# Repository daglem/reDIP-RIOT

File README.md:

# reDIP RIOT

## MOS 6530 RRIOT / MOS 6532 RIOT FPGA replacement

## Overview
The reDIP RIOT is an open source FPGA board which combines the following in a DIP-40 size package:

* Lattice iCE40UP5K FPGA
* 1Mbit FLASH
* 5V tolerant I/O

The reDIP RIOT provides an open source hardware platform for 6530 RRIOT / MOS 6532 RIOT replacements.

Designs for the iCE40UP5K FPGA can be processed by [yosys](https://github.com/YosysHQ/yosys/) and [nextpnr](https://github.com/YosysHQ/nextpnr/).

## I/O interfaces

### DIP-40 header pins:

* 5V input
* 35 FPGA GPIO
* 3 FPGA open-drain I/O
* GND

All FPGA header I/O is 5V tolerant, and can drive 5V TTL.

### SPI / programming header:

A separate header footprint is provided for (Q)SPI flash programming, with pinout borrowed from the [iCEBreaker Bitsy](https://github.com/icebreaker-fpga/icebreaker).

## Board Front

## Board Back

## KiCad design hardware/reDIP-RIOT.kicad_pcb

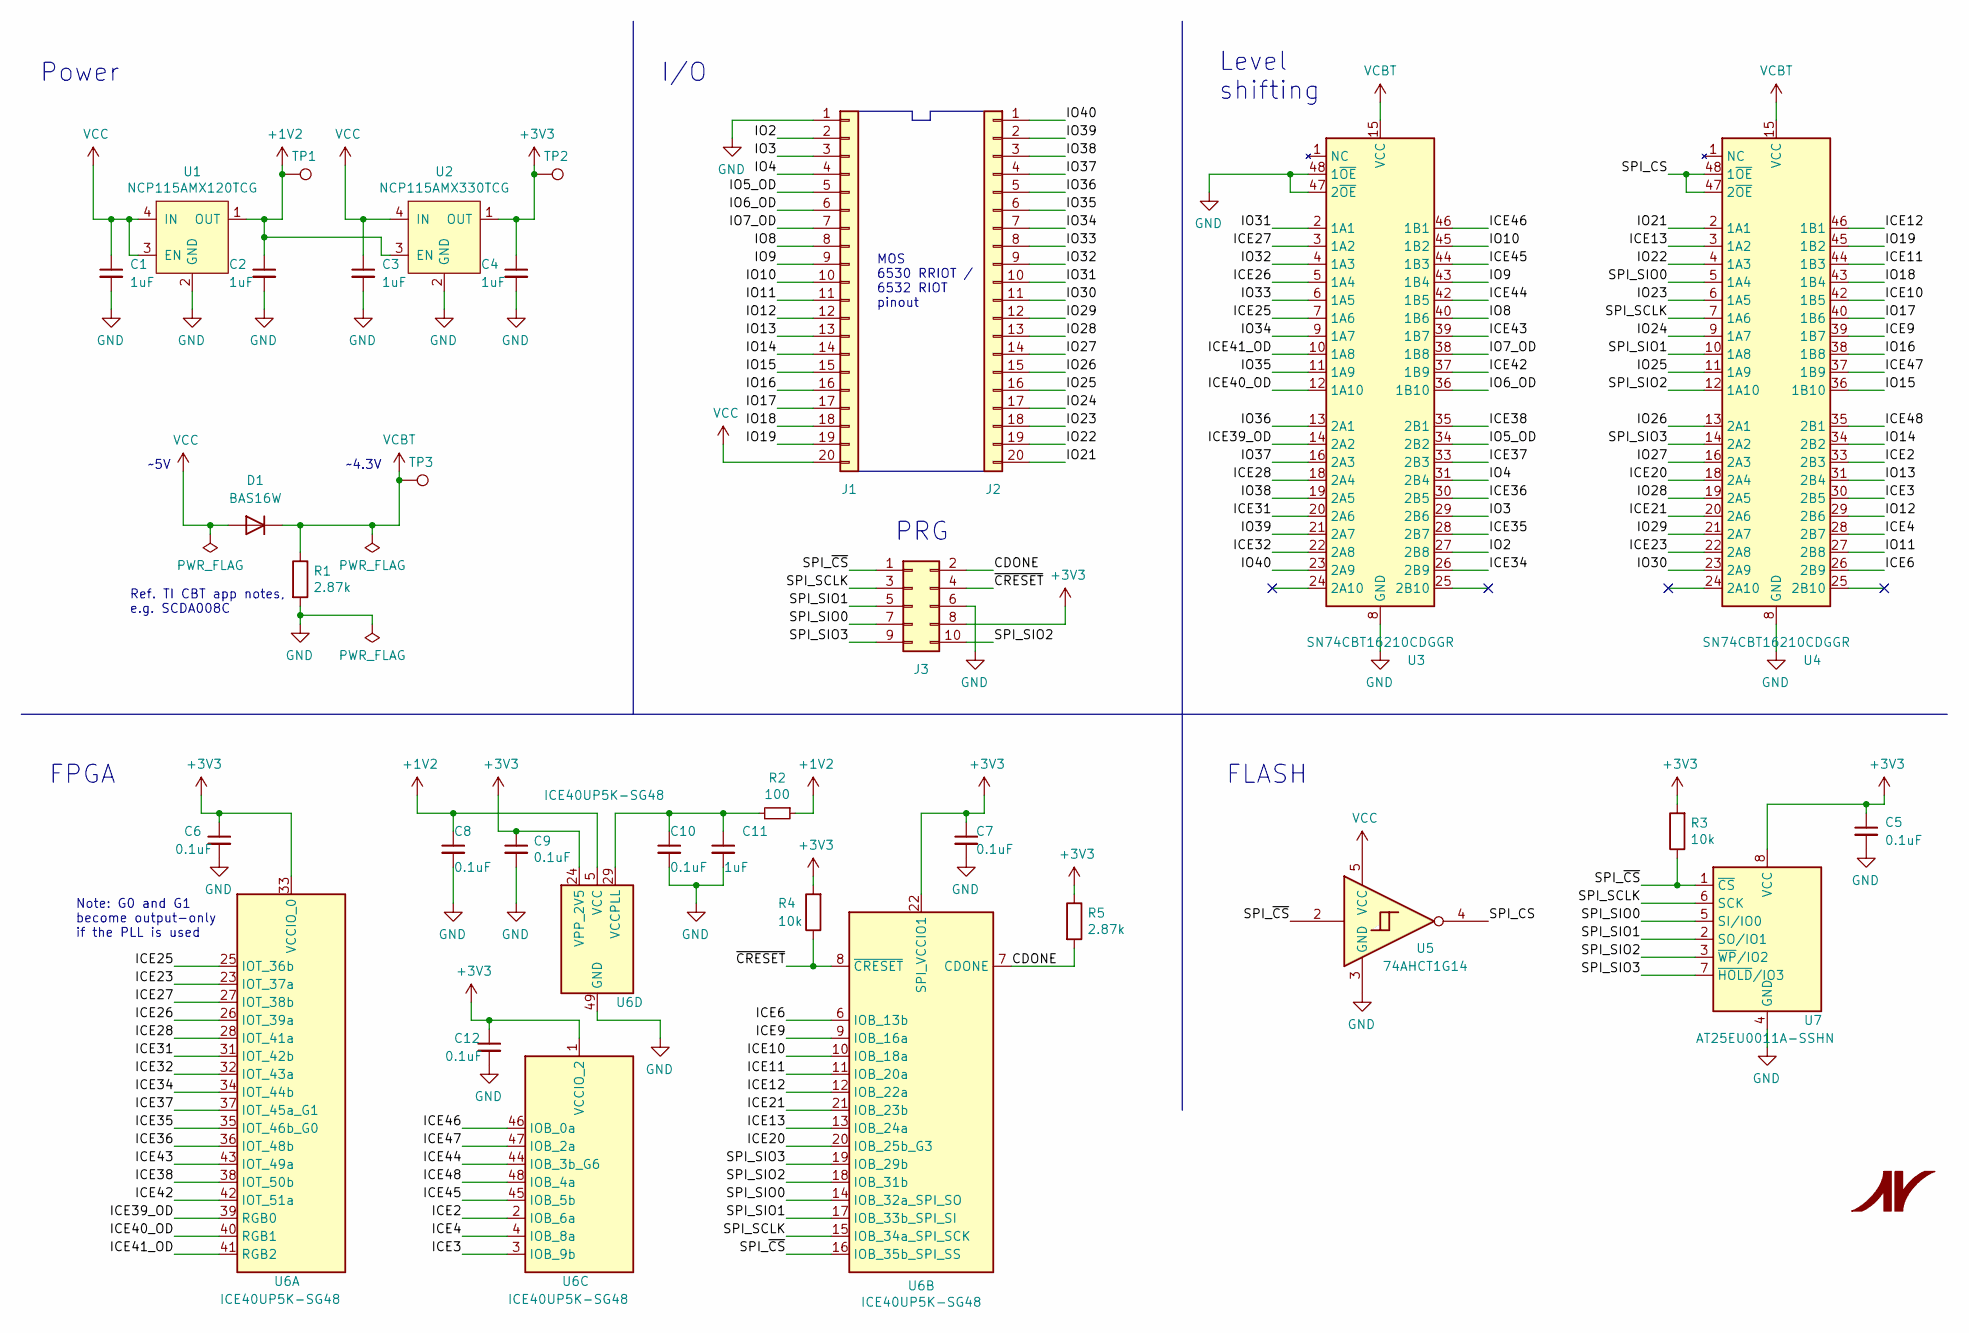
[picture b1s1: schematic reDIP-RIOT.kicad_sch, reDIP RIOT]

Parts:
C1, C3: 1uF; C_0402_1005Metric
C2, C4, C11: 1uF; C_0201_0603Metric
C5, C6, C7, C8, C9, C10, C12: 0.1uF; C_0201_0603Metric
D1: BAS16W; SOT-323_SC-70
J1, J2: Conn_01x20; PinHeader_1x20_P2.54mm_Vertical_Machined
J3: Conn_02x05_Odd_Even; PinHeader_2x05_P2.54mm_Vertical
R1, R5: 2.87k; R_0201_0603Metric
R2: 100; R_0201_0603Metric
R3, R4: 10k; R_0201_0603Metric
TP1, TP2, TP3: TestPoint; TestPoint_Pad_D1.00mm
U1: NCP115AMX120TCG; CASE_711AJ_1.0x1.0mm_P0.65mm
U2: NCP115AMX330TCG; CASE_711AJ_1.0x1.0mm_P0.65mm
U3, U4: SN74CBT16210CDGGR; TSSOP-48_6.1x12.5mm_P0.5mm
U5: 74AHCT1G14; SOT-353_SC-70-5
U6: ICE40UP5K-SG48; QFN-48-1EP_7x7mm_P0.5mm_EP5.6x5.6mm
U7: AT25EU0011A-SSHN; SOIC-8_3.9x4.9mm_P1.27mm

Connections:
+1V2: C2.1, C8.1, R2.1, TP1.1, U1.1 (OUT), U2.3 (EN), U6.5 (VCC), U6.30 (VCC)
+3V3: C4.1, C5.1, C6.1, C7.1, C9.1, C12.1, J3.8, R3.2, R4.2, R5.1, TP2.1, U2.1 (OUT), U6.1 (VCCIO_2), U6.22 (SPI_VCCIO1), U6.24 (VPP_2V5), U6.33 (VCCIO_0), U7.8 (VCC)
/CDONE: J3.2, R5.2, U6.7 (CDONE)
/ICE2: U4.33 (2B3), U6.2 (IOB_6a)
/ICE3: U4.30 (2B5), U6.3 (IOB_9b)
/ICE4: U4.28 (2B7), U6.4 (IOB_8a)
/ICE6: U4.26 (2B9), U6.6 (IOB_13b)
/ICE9: U4.39 (1B7), U6.9 (IOB_16a)
/ICE10: U4.42 (1B5), U6.10 (IOB_18a)
/ICE11: U4.44 (1B3), U6.11 (IOB_20a)
/ICE12: U4.46 (1B1), U6.12 (IOB_22a)
/ICE13: U4.3 (1A2), U6.13 (IOB_24a)
/ICE20: U4.18 (2A4), U6.20 (IOB_25b_G3)
/ICE21: U4.20 (2A6), U6.21 (IOB_23b)
/ICE23: U4.22 (2A8), U6.23 (IOT_37a)
/ICE25: U3.7 (1A6), U6.25 (IOT_36b)
/ICE26: U3.5 (1A4), U6.26 (IOT_39a)
/ICE27: U3.3 (1A2), U6.27 (IOT_38b)
/ICE28: U3.18 (2A4), U6.28 (IOT_41a)
/ICE31: U3.20 (2A6), U6.31 (IOT_42b)
/ICE32: U3.22 (2A8), U6.32 (IOT_43a)
/ICE34: U3.26 (2B9), U6.34 (IOT_44b)
/ICE35: U3.28 (2B7), U6.35 (IOT_46b_G0)
/ICE36: U3.30 (2B5), U6.36 (IOT_48b)
/ICE37: U3.33 (2B3), U6.37 (IOT_45a_G1)
/ICE38: U3.35 (2B1), U6.38 (IOT_50b)
/ICE39_OD: U3.14 (2A2), U6.39 (RGB0)
/ICE40_OD: U3.12 (1A10), U6.40 (RGB1)
/ICE41_OD: U3.10 (1A8), U6.41 (RGB2)
/ICE42: U3.37 (1B9), U6.42 (IOT_51a)
/ICE43: U3.39 (1B7), U6.43 (IOT_49a)
/ICE44: U3.42 (1B5), U6.44 (IOB_3b_G6)
/ICE45: U3.44 (1B3), U6.45 (IOB_5b)
/ICE46: U3.46 (1B1), U6.46 (IOB_0a)
/ICE47: U4.37 (1B9), U6.47 (IOB_2a)
/ICE48: U4.35 (2B1), U6.48 (IOB_4a)
/IO2: J1.2, U3.27 (2B8)
/IO3: J1.3, U3.29 (2B6)
/IO4: J1.4, U3.31 (2B4)
/IO5_OD: J1.5, U3.34 (2B2)
/IO6_OD: J1.6, U3.36 (1B10)
/IO7_OD: J1.7, U3.38 (1B8)
/IO8: J1.8, U3.40 (1B6)
/IO9: J1.9, U3.43 (1B4)
/IO10: J1.10, U3.45 (1B2)
/IO11: J1.11, U4.27 (2B8)
/IO12: J1.12, U4.29 (2B6)
/IO13: J1.13, U4.31 (2B4)
/IO14: J1.14, U4.34 (2B2)
/IO15: J1.15, U4.36 (1B10)
/IO16: J1.16, U4.38 (1B8)
/IO17: J1.17, U4.40 (1B6)
/IO18: J1.18, U4.43 (1B4)
/IO19: J1.19, U4.45 (1B2)
/IO21: J2.20, U4.2 (1A1)
/IO22: J2.19, U4.4 (1A3)
/IO23: J2.18, U4.6 (1A5)
/IO24: J2.17, U4.9 (1A7)
/IO25: J2.16, U4.11 (1A9)
/IO26: J2.15, U4.13 (2A1)
/IO27: J2.14, U4.16 (2A3)
/IO28: J2.13, U4.19 (2A5)
/IO29: J2.12, U4.21 (2A7)
/IO30: J2.11, U4.23 (2A9)
/IO31: J2.10, U3.2 (1A1)
/IO32: J2.9, U3.4 (1A3)
/IO33: J2.8, U3.6 (1A5)
/IO34: J2.7, U3.9 (1A7)
/IO35: J2.6, U3.11 (1A9)
/IO36: J2.5, U3.13 (2A1)
/IO37: J2.4, U3.16 (2A3)
/IO38: J2.3, U3.19 (2A5)
/IO39: J2.2, U3.21 (2A7)
/IO40: J2.1, U3.23 (2A9)
/SPI_CS: U4.47 (2~OE), U4.48 (1~OE), U5.4
/SPI_SCLK: J3.3, U4.7 (1A6), U6.15 (IOB_34a_SPI_SCK), U7.6 (SCK)
/SPI_SIO0: J3.7, U4.5 (1A4), U6.14 (IOB_32a_SPI_SO), U7.5 (SI/IO0)
/SPI_SIO1: J3.5, U4.10 (1A8), U6.17 (IOB_33b_SPI_SI), U7.2 (SO/IO1)
/SPI_SIO2: J3.10, U4.12 (1A10), U6.18 (IOB_31b), U7.3 (~WP/IO2)
/SPI_SIO3: J3.9, U4.14 (2A2), U6.19 (IOB_29b), U7.7 (~HOLD/IO3)
/SPI_~CS: J3.1, R3.1, U5.2, U6.16 (IOB_35b_SPI_SS), U7.1 (~CS)
/~CRESET: J3.4, R4.1, U6.8 (~CRESET)
GND: C1.2, C2.2, C3.2, C4.2, C5.2, C6.2, C7.2, C8.2, C9.2, C10.2, C11.2, C12.2, J1.1, J3.6, R1.2, U1.2 (GND), U2.2 (GND), U3.8 (GND), U3.17 (GND), U3.32 (GND), U3.41 (GND), U3.47 (2~OE), U3.48 (1~OE), U4.8 (GND), U4.17 (GND), U4.32 (GND), U4.41 (GND), U5.3 (GND), U6.49 (GND), U7.4 (GND)
unnamed: C10.1, C11.1, R2.2, U6.29 (VCCPLL)
VCBT: D1.3 (K), R1.1, TP3.1, U3.15 (VCC), U4.15 (VCC)
VCC: C1.1, C3.1, D1.1 (A), J1.20, U1.3 (EN), U1.4 (IN), U2.4 (IN), U5.5 (VCC)

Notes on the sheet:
MOS 6530 RRIOT / 6532 RIOT pinout
PRG
Ref. TI CBT app notes, e.g. SCDA008C
~4.3V
FLASH
FPGA
Power
I/O
Level shifting
~5V
Note: G0 and G1 become output-only if the PLL is used

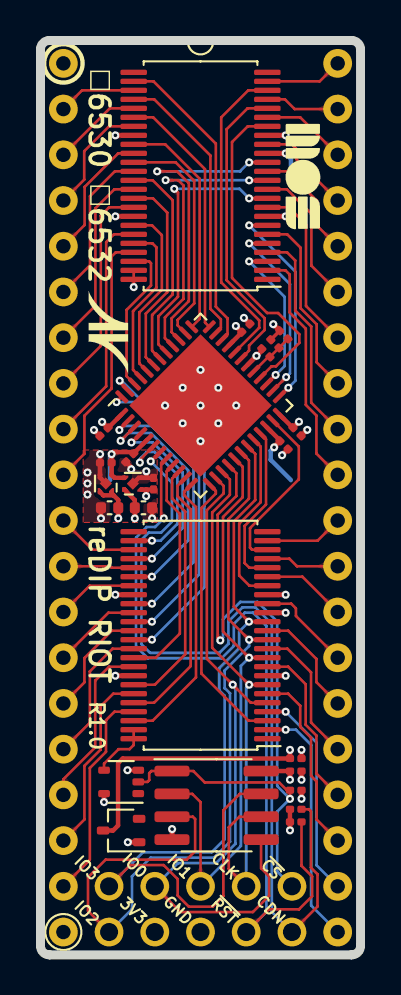
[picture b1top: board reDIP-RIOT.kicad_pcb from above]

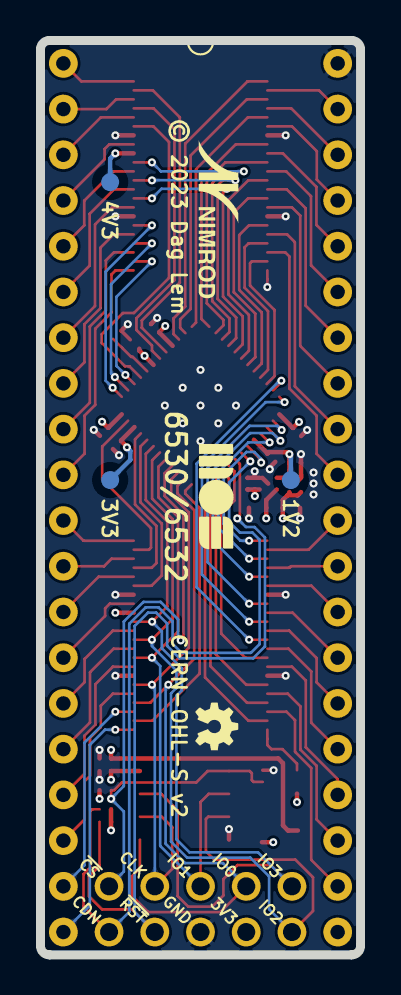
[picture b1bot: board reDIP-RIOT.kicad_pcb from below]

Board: 4 copper layers, 17.8 x 50.8 mm, 40 parts (14 on the bottom side), 86 nets.

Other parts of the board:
SolderMask_D0.25mm, SolderMask_D0.25mm#2, SolderMask_D0.25mm#3, SolderMask_D0.25mm#4, SolderMask_D0.25mm#5, SolderMask_D0.25mm#6, SolderMask_D0.25mm#7, SolderMask_D0.25mm#8, SolderMask_D0.25mm#9: SolderMask_D0.25mm

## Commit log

2023-10-02 Added CRESET pull-up, removed CDONE LED
2023-10-03 Cleanup
    * Removed unused footprints
    * Rounded rectangle pads for SOT footprints
    * Increased drill to 0.8mm for header pins
    * Corrected BOM text
2023-10-04 Added example pin headers to BOM
2023-10-06 LDO ground planes, via teardrops
2023-10-06 Use 74AHCT1G14 for better signal level margins
2023-10-09 Power supply for 74AHCT1G14 within range
2023-11-04 Replaced iCE5LP1K with iCE40UP5K
    The MOS 6530 and MOS 6532 have on-chip data port pull-up resistors
    in the range of 5k.
    While the iCE40UP5K features configurable 3.3k/6.8k/10k/100k pull-up
    resistors, the iCE5LP1K only features 100k pull-up resistors.
    We make the simple fix of using the more capable (and somewhat more
    expensive) pin compatible iCE40UP5K, instead of adding physical
2024-08-12 Add configuration for pull-up resistors

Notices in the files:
hardware/reDIP-RIOT.kicad_pcb:
© 2023 Dag Lem
Licensed under CERN-OHL-S v2 (https://ohwr.org/cern_ohl_s_v2.txt)
CERN-OHL-S v2
